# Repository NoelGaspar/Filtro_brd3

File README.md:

# Filtro_brd3
Flitro cascada para señal de control de bomba

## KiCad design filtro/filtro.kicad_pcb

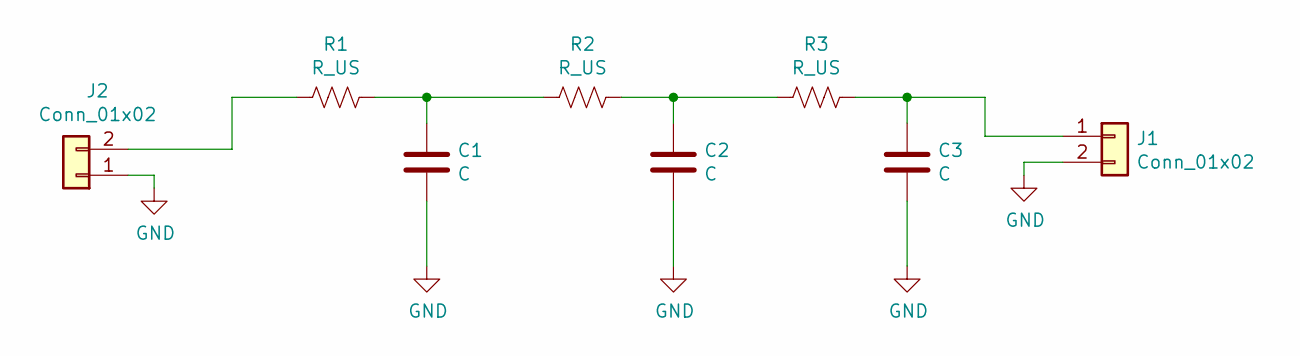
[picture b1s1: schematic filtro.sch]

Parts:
C1, C2, C3: C; C_Rect_L4.6mm_W2.0mm_P2.50mm_MKS02_FKP02
J1, J2: Conn_01x02; Tb-2x1-5p-TH-V
R1, R2, R3: R_US; R_Axial_DIN0204_L3.6mm_D1.6mm_P1.90mm_Vertical

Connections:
GND: C1.2, C2.2, C3.2, J1.2, J2.1
unnamed: C1.1, R1.2, R2.1
unnamed: C2.1, R2.2, R3.1
unnamed: C3.1, J1.1, R3.2
unnamed: J2.2, R1.1

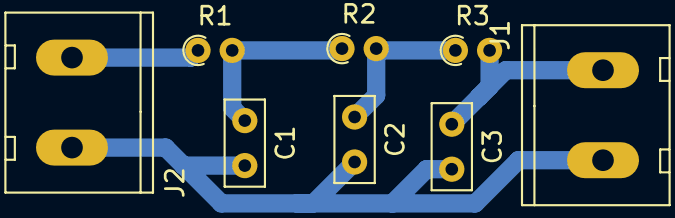
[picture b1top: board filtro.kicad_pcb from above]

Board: 2 copper layers, 8 parts (0 on the bottom side), 5 nets.

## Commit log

2021-08-09 adding board design files
